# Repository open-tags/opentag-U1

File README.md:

# opentag U1

UWB distance and indoor positioning hardware for robots: KiCad design, Rust
firmware, host tools, enclosure CAD and bench test notes. Everything in this
repository is released under the [MIT License](LICENSE).

Product page and kits: <https://open-tags.com/products/u1/> ·
Documentation: <https://open-tags.com/docs/> ·
Measured performance: <https://open-tags.com/validation/>

## Contents

| Folder | What it holds |
| --- | --- |
| [`hardware/`](hardware/) | KiCad project for U1 PCB V2.2 (4 layers, STM32G474 + Qorvo DWM3000), schematic PDF, part list, and fabrication outputs (Gerbers + drill) |
| [`firmware/stm32g4/`](firmware/stm32g4/) | Embassy (Rust) firmware: two-way ranging, TDOA anchor/tag, USB serial, CAN FD, and board bring-up examples |
| [`firmware/twr_plot/`](firmware/twr_plot/) | Host-side plotting, localization, and calibration tools (Rust) |
| [`mechanical/`](mechanical/) | Enclosure STEP files (assembly, case, lid) and a printable case `.3mf`; also on [Onshape](https://cad.onshape.com/documents/432dec42a257744f3b8f22d9/w/829cba9d7a4b997211a6277e/e/23eb042ed87c06c15fa7c407) |
| [`testing/`](testing/) | Bench test notes for two-way ranging and TDOA |

The ROS 2 driver and the Python host scripts live with the website source at
[open-tags/open-tags.github.io](https://github.com/open-tags/open-tags.github.io)
(`ros2/` and `docs/scripts/`).

## Hardware

Open `hardware/opentag.kicad_pro` in KiCad 10. Footprints are embedded in the
board file. Three vendor 3D models are not redistributed here, so they appear
missing in the 3D viewer until you add them to `hardware/footprints/`:

- `1473790000--3DModel-STEP-764301.STEP`: Weidmüller 1473790000 terminal block (from Weidmüller)
- `3220-10-0300-00 3D.stp`: CNC Tech 3220-10-0300-00 SWD header (from CNC Tech)
- `v2 - dip_switch.step`: DIP switch body

`hardware/fabrication/` was generated from the board file with `kicad-cli`.

## Firmware

Requires Rust with the `thumbv7em-none-eabi` target and
[probe-rs](https://probe.rs) with an ST-Link or other SWD probe.

```sh
rustup target add thumbv7em-none-eabi
cd firmware/stm32g4
cargo run --release --bin twr_resp    # build, flash, and stream defmt logs
```

`tdoa_bench` needs `TDOA_ROLE=master` or `TDOA_ROLE=anchor` at build time.
Cargo fetches Embassy from GitHub at a pinned commit. See
[`firmware/README.md`](firmware/README.md) for the binaries, pinout, and
flashing, and [`firmware/RANGE_CAN.md`](firmware/RANGE_CAN.md) for the
range-over-CAN build.

## Third-party code

Several bring-up examples in `firmware/stm32g4/src/bin/` are adapted from the
[Embassy](https://github.com/embassy-rs/embassy) STM32G4 examples (MIT OR
Apache-2.0). Dependencies keep their own licenses; see each crate on crates.io.

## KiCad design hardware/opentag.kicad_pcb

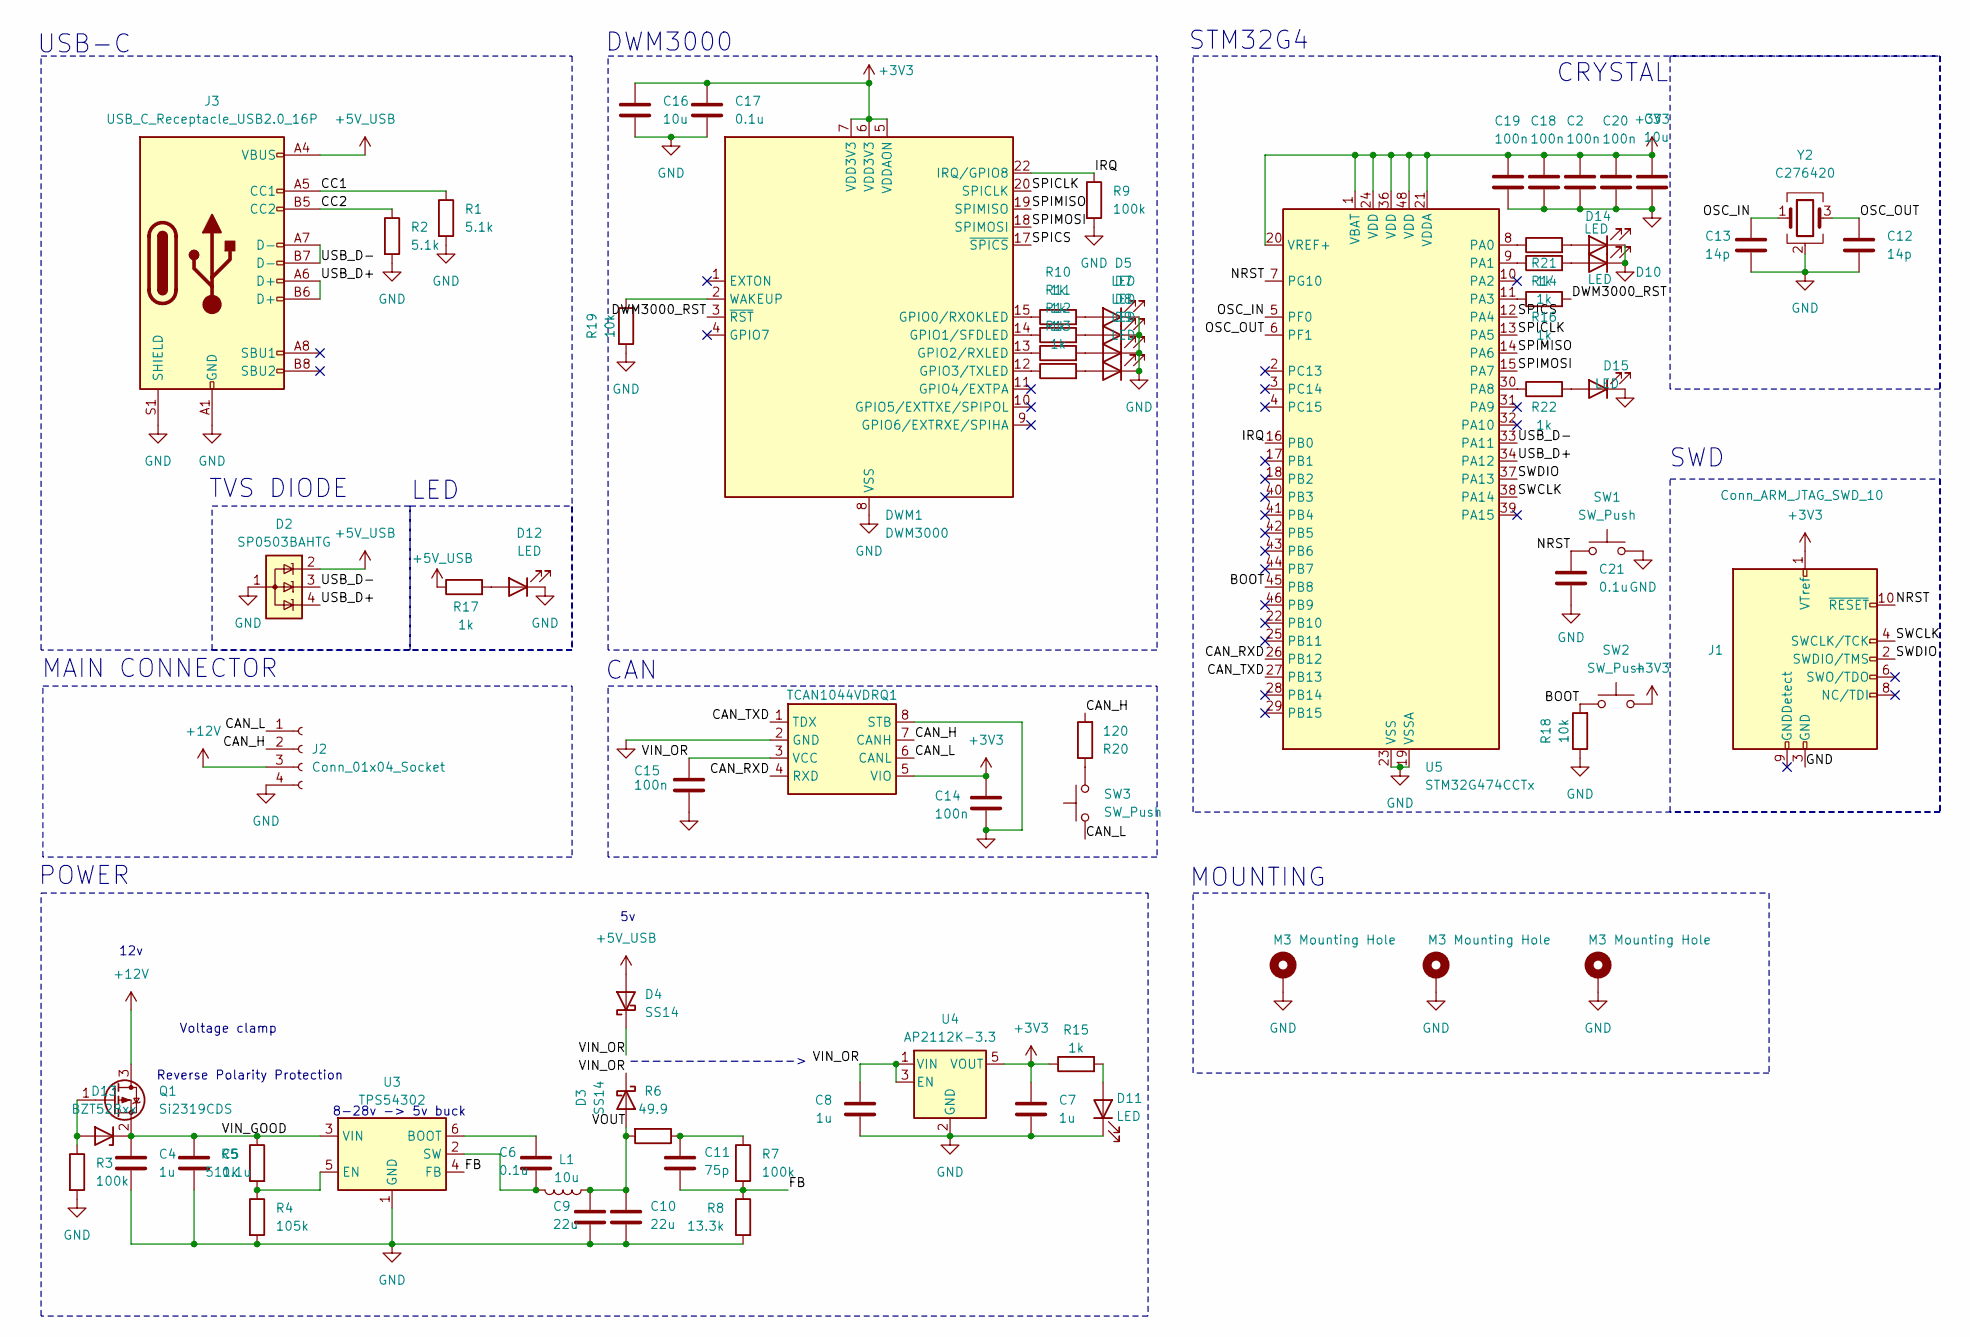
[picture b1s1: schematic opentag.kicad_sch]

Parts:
C2, C14, C15, C18, C19, C20: 100n; C_0402_1005Metric_Pad0.74x0.62mm_HandSolder; LCSC C307331
C3, C16: 10u; C_0402_1005Metric_Pad0.74x0.62mm_HandSolder; LCSC C315248
C4, C8: 1u; C_0402_1005Metric_Pad0.74x0.62mm_HandSolder; LCSC C1518208
C5, C6, C17, C21: 0.1u; C_0402_1005Metric_Pad0.74x0.62mm_HandSolder; LCSC C307331
C7: 1u; C_0402_1005Metric_Pad0.74x0.62mm_HandSolder; LCSC C29266
C9, C10: 22u; C_0402_1005Metric_Pad0.74x0.62mm_HandSolder; LCSC C105226
C11: 75p; C_0402_1005Metric_Pad0.74x0.62mm_HandSolder; LCSC C107010
C12, C13: 14p; C_0402_1005Metric_Pad0.74x0.62mm_HandSolder; LCSC C458857
D2: SP0503BAHTG; SOT-143; LCSC C3040626
D3, D4: SS14; D_SMA; LCSC C2480
D5, D7, D8, D9, D10, D11, D12, D14, D15: LED; LED_0402_1005Metric_Pad0.77x0.64mm_HandSolder; LCSC C130719
D13: BZT52Bxx; D_SOD-123F; LCSC C282531
DWM1: DWM3000; DWM1000; Mouser Part Number 772-DWM3000TR13; Digikey Part Number 2312-DWM3000TR13CT-ND
H1, H2, H3: M3 Mounting Hole; MountingHole_3.2mm_M3_Pad_Via
J1: Conn_ARM_JTAG_SWD_10; PinHeader_2x05_P1.27mm_Vertical_SMD; LCSC C42372555
J2: Conn_01x04_Socket; 4_WIRE_1473790000; Mouser Part Number 470-1473790000; Digikey Part Number 281-6806-1-ND
J3: USB_C_Receptacle_USB2.0_16P; USB_C_Receptacle_XKB_U262-16XN-4BVC11; LCSC C319148
L1: 10u; L_Sunlord_MWSA0503S; LCSC C408412
Q1: Si2319CDS; SOT-23; LCSC C5122036
R1, R2: 5.1k; R_0402_1005Metric_Pad0.72x0.64mm_HandSolder; LCSC C25905
R3, R7, R9: 100k; R_0402_1005Metric_Pad0.72x0.64mm_HandSolder; LCSC C25530
R4: 105k; R_0402_1005Metric_Pad0.72x0.64mm_HandSolder; LCSC C25742
R5: 511k; R_0402_1005Metric_Pad0.72x0.64mm_HandSolder; LCSC C64042
R6: 49.9; R_0402_1005Metric_Pad0.72x0.64mm_HandSolder; LCSC C325388
R8: 13.3k; R_0402_1005Metric_Pad0.72x0.64mm_HandSolder; LCSC C122547
R10, R11, R12, R13, R14, R15, R16, R17, R21, R22: 1k; R_0402_1005Metric_Pad0.72x0.64mm_HandSolder; LCSC C11702
R18, R19: 10k; R_0402_1005Metric_Pad0.72x0.64mm_HandSolder; LCSC C25744
R20: 120; R_0402_1005Metric_Pad0.72x0.64mm_HandSolder; LCSC C100218
SW1, SW2: SW_Push; SW_SPST_EVQP2_ShortPushTravel_H2.1mm; LCSC C79161
SW3: SW_Push; THS101J; LCSC C2758165
U1: TCAN1044VDRQ1; SOIC-8_3.9x4.9mm_P1.27mm; LCSC C1852061
U3: TPS54302; SOT-23-6; LCSC C311983
U4: AP2112K-3.3; SOT-23-5; LCSC C23380830
U5: STM32G474CCTx; LQFP-48_7x7mm_P0.5mm; LCSC C730124
Y2: C276420; Crystal_SMD_Abracon_ABM3B-4Pin_5.0x3.2mm; LCSC C276420

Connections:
+3V3: C2.1, C3.1, C7.1, C14.1, C16.1, C17.1, C18.1, C19.1, C20.1, DWM1.5 (VDDAON), DWM1.6 (VDD3V3), DWM1.7 (VDD3V3), J1.1 (VTref), R15.1, SW2.2, U1.5 (VIO), U4.5 (VOUT), U5.1 (VBAT), U5.20 (VREF+), U5.21 (VDDA), U5.24 (VDD), U5.36 (VDD), U5.48 (VDD)
+5V_USB: D2.2 (K), D4.2 (A), J3.A4 (VBUS), J3.A9 (VBUS), J3.B4 (VBUS), J3.B9 (VBUS), R17.1
+12V: J2.3, Q1.3 (D)
/BOOT: R18.2, SW2.1, U5.45 (PB8)
/CAN_H: J2.2, R20.2, U1.7 (CANH)
/CAN_L: J2.1, SW3.1, U1.6 (CANL)
/CAN_RXD: U1.4 (RXD), U5.26 (PB12)
/CAN_TXD: U1.1 (TDX), U5.27 (PB13)
/CC1: J3.A5 (CC1), R1.1
/CC2: J3.B5 (CC2), R2.1
/DWM3000_RST: DWM1.3 (~RST), R16.2
/FB: C11.2, R7.2, R8.1, U3.4 (FB)
/IRQ: DWM1.22 (IRQ/GPIO8), R9.1, U5.16 (PB0)
/NRST: C21.1, J1.10 (~RESET), SW1.1, U5.7 (PG10)
/OSC_IN: C13.1, U5.5 (PF0), Y2.1
/OSC_OUT: C12.1, U5.6 (PF1), Y2.3
/SPICLK: DWM1.20 (SPICLK), U5.13 (PA5)
/SPICS: DWM1.17 (~SPICS), U5.12 (PA4)
/SPIMISO: DWM1.19 (SPIMISO), U5.14 (PA6)
/SPIMOSI: DWM1.18 (SPIMOSI), U5.15 (PA7)
/SWCLK: J1.4 (SWCLK/TCK), U5.38 (PA14)
/SWDIO: J1.2 (SWDIO/TMS), U5.37 (PA13)
/USB_D+: D2.4 (K), J3.A6 (D+), J3.B6 (D+), U5.34 (PA12)
/USB_D-: D2.3 (K), J3.A7 (D-), J3.B7 (D-), U5.33 (PA11)
/VIN_GOOD: C4.1, C5.1, D13.1 (K), Q1.2 (S), R5.1, U3.3 (VIN)
/VIN_OR: C8.1, C15.1, D3.1 (K), D4.1 (K), U1.3 (VCC), U4.1 (VIN), U4.3 (EN)
/VOUT: C9.1, C10.1, D3.2 (A), L1.1, R6.2
GND: C2.2, C3.2, C4.2, C5.2, C7.2, C8.2, C9.2, C10.2, C12.2, C13.2, C14.2, C15.2, C16.2, C17.2, C18.2, C19.2, C20.2, C21.2, D2.1 (A), D5.1 (K), D7.1 (K), D8.1 (K), D9.1 (K), D10.1 (K), D11.1 (K), D12.1 (K), D14.1 (K), D15.1 (K), DWM1.8 (VSS), DWM1.16 (VSS), DWM1.21 (VSS), DWM1.23 (VSS), DWM1.24 (VSS), H1.1 (1_1), H2.1 (1_1), H3.1 (1_1), J1.3 (GND), J1.5 (GND), J2.4, J3.A1 (GND), J3.A12 (GND), J3.B1 (GND), J3.B12 (GND), J3.S1 (SHIELD), R1.2, R2.2, R3.2, R4.2, R8.2, R9.2, R18.1, R19.1, SW1.2, U1.2 (GND), U1.8 (STB), U3.1 (GND), U4.2 (GND), U5.19 (VSSA), U5.23 (VSS), U5.35 (VSS), U5.47 (VSS), Y2.2 (G), Y2.4 (G)
unnamed: C11.1, R6.1, R7.1
unnamed: D5.2 (A), R10.2
unnamed: D7.2 (A), R11.2
unnamed: D8.2 (A), R12.2
unnamed: D9.2 (A), R13.2
unnamed: D10.2 (A), R14.2
unnamed: D11.2 (A), R15.2
unnamed: D12.2 (A), R17.2
unnamed: D13.2 (A), Q1.1 (G), R3.1
unnamed: D14.2 (A), R21.2
unnamed: D15.2 (A), R22.2
unnamed: DWM1.15 (GPIO0/RXOKLED), R10.1
unnamed: DWM1.14 (GPIO1/SFDLED), R11.1
unnamed: DWM1.13 (GPIO2/RXLED), R12.1
unnamed: DWM1.12 (GPIO3/TXLED), R13.1
unnamed: DWM1.2 (WAKEUP), R19.2
unnamed: R20.1, SW3.2
unnamed: C6.1, U3.6 (BOOT)
unnamed: R4.1, R5.2, U3.5 (EN)
unnamed: C6.2, L1.2, U3.2 (SW)
unnamed: R21.1, U5.8 (PA0)
unnamed: R14.1, U5.9 (PA1)
unnamed: R16.1, U5.11 (PA3)
unnamed: R22.1, U5.30 (PA8)

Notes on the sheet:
MOUNTING
SWD
LED
DWM3000
TVS DIODE
--------------->
Reverse Polarity Protection
8-28v -> 5v buck
Voltage clamp
CAN
POWER
USB-C
12v
STM32G4
CRYSTAL
MAIN CONNECTOR

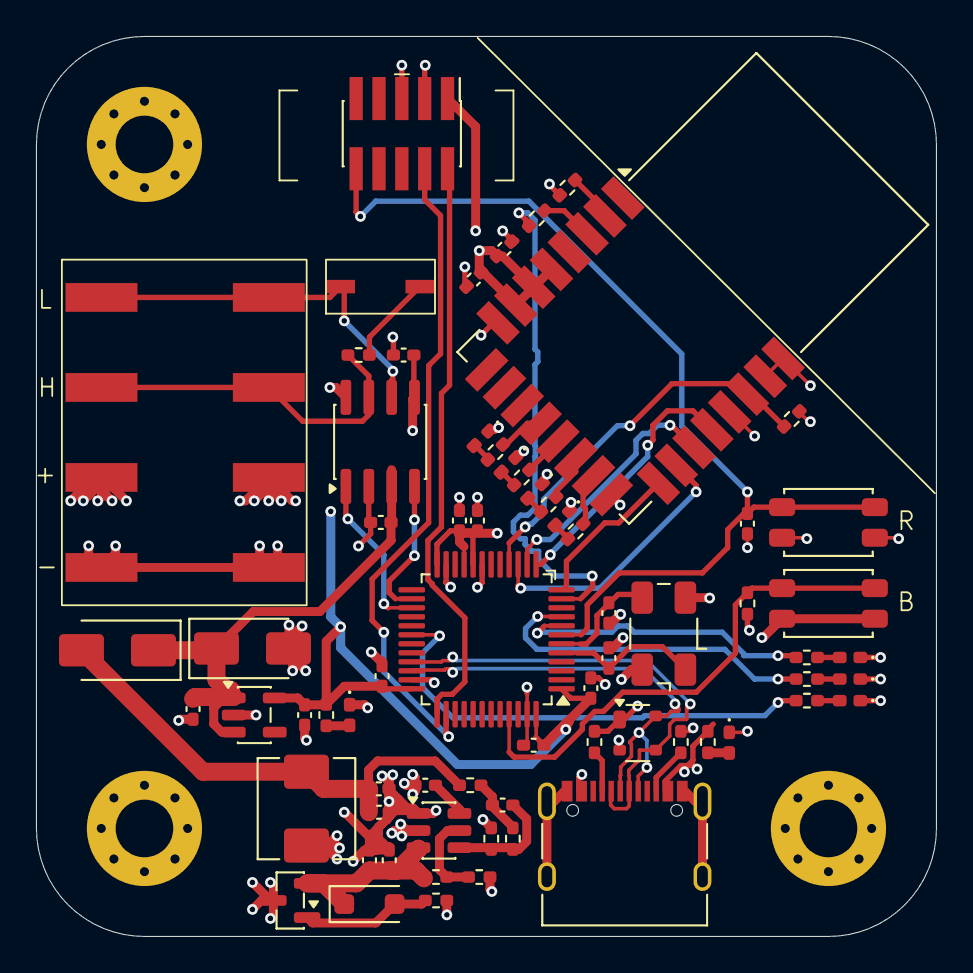
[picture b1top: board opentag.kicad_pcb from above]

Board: 4 copper layers, 50.0 x 50.0 mm, 72 parts (0 on the bottom side), 52 nets.

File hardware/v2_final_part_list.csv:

Comment,Designator,Footprint,JLCPCB Part #,Qty,Ext.Price($)
LED,"D14,D5,D7,D8,D9",0402,C965793,62,0.49
AP2112K-3.3,U4,SOT-23-5,C23380830,12,1.29
Si2319CDS,Q1,SOT-23,C5122036,12,1.11
511k,R5,0402,C64042,20,0.02
SW_Push,"SW1,SW2",SW_SPST_EVQP2_ShortPushTravel_H2.1mm,C79161,20,7.51
BZT52Bxx,D13,D_SOD-123F,C282531,14,0.63
105k,R4,0402,C25742,20,0.01
LED,D15,0402,C25503345,22,0.18
LED,D10,0402,C25503856,20,0.26
Conn_ARM_JTAG_SWD_10,J1,PinHeader_2x05_P1.27mm_Vertical_SMD,C42372555,10,1.91
22u,"C10,C9",0402,C3845593,21,2.95
LED,"D11,D12",0402,C20613596,32,0.36
SP0503BAHTG,D2,SOT-143,C3040626,12,1.13
10u,"C16,C3",0402,C315248,32,0.29
120,R20,0402,C25079,20,0.02
10u,L1,L_Sunlord_MWSA0503S,C408412,12,2.03
75p,C11,0402,C107010,20,0.02
TPS54302,U3,SOT-23-6,C311983,10,2.44
USB_C_Receptacle_USB2.0_16P,J3,USB_C_Receptacle_XKB_U262-16XN-4BVC11,C319148,10,3.70
SS14,"D3,D4",D_SMA,C2480,30,0.50
100k,"R3,R7,R9",0402,C25530,40,0.03
1k,"R10,R11,R12,R13,R14,R15,R16,R17,R21,R22",0402,C11702,110,0.11
1u,"C4,C7,C8",0402,C1518208,34,1.03
49.9,R6,0402,C325388,20,0.05
13.3k,R8,0402,C122547,20,0.02
5.1k,"R1,R2",0402,C25905,30,0.03
SW_Push,SW3,THS101J,C2758165,10,5.99
Crystal_GND24,Y2,Crystal_SMD_Abracon_ABM3B-4Pin_5.0x3.2mm,C276420,10,6.18
14p,"C12,C13",0402,C458857,30,0.06
TCAN1044VDRQ1,U1,SOIC-8_3.9x4.9mm_P1.27mm,C1852061,10,3.39
100n,"C17,C21,C5,C6,C14,C15,C18,C19,C2,C20",0402,C307331,110,0.46
10k,"R18,R19",0402,C25744,30,0.04
STM32G474CCTx,U5,LQFP-48_7x7mm_P0.5mm,C730124,10,29.39

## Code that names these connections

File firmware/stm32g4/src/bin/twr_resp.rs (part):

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    }
    let p = embassy_stm32::init(config);
    #[cfg(feature = "range-can")]
    let can = range_can::configure(p.FDCAN2, p.PB12, p.PB13);

    // Pull the patched calibration default out of flash. read_volatile
    // prevents the optimizer from constant-folding it (which would
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
    info!("twr_resp starting (calib={})", initial_calib);

    let mut rst = Output::new(p.PA3, Level::Low, Speed::Low);
    Timer::after_millis(10).await;
    rst.set_high();
    Timer::after_millis(5).await;
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    let mut spi_config = spi::Config::default();
    spi_config.frequency = Hertz(4_000_000);
    let spi = Spi::new(
        p.SPI1, p.PA5, p.PA7, p.PA6, p.DMA1_CH3, p.DMA1_CH2, Irqs, spi_config,
    );
    let cs = Output::new(p.PA4, Level::High, Speed::High);
    let spi_dev = ExclusiveDevice::new(spi, cs, Delay).unwrap();

    let dw3000 = DW3000::new(spi_dev);
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    }
    dw3000.gpio_config_clocks().await.expect("gpio clocks");

    let driver = Driver::new(p.USB, Irqs, p.PA12, p.PA11);
    let mut usb_config = embassy_usb::Config::new(0xc0de, 0xcafe);
    usb_config.manufacturer = Some("opentags");
    usb_config.product = Some("opentags TWR Responder");
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
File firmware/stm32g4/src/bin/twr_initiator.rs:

#![no_std]
#![no_main]

// TWR Initiator — Qorvo APS013 Double-Sided Two-Way Ranging (DS-TWR)
//
// 3-message exchange:
//   Msg 1  Poll     Initiator → Responder    seq                     (4 B)
//   Msg 2  Response Responder → Initiator    seq + T2(5B) + T3(5B)   (14 B)
//   Msg 3  Final    Initiator → Responder    seq + T1(5B) + T4(5B) + T5(5B) (19 B)
//
// Timestamps (all 40-bit DW3000 DTU, little-endian 5 bytes):
//   T1 = initiator TX Poll
//   T2 = responder RX Poll      (embedded in Response)
//   T3 = responder TX Response  (embedded in Response, via delayed TX)
//   T4 = initiator RX Response
//   T5 = initiator TX Final     (pre-calculated, embedded in Final, via delayed TX)
//   T6 = responder RX Final     (used at responder to compute distance)
//
// Distance is computed and logged by the responder (it holds all 6 timestamps).
// Formula (APS013):
//   tof = (Tround1 × Tround2 - Treply1 × Treply2) / (Tround1 + Tround2 + Treply1 + Treply2)
//   where  Tround1 = T4-T1,  Tround2 = T6-T3,  Treply1 = T3-T2,  Treply2 = T5-T4
//
// Pinout:
//   PA3=RST  PA4=CS  PA5=SCK  PA6=MISO  PA7=MOSI
//   PA0=Poll TX LED  PA1=exchange OK LED  PA8=miss/error LED

use defmt::*;
use embassy_executor::Spawner;
use embassy_stm32::gpio::{Level, Output, Speed};
use embassy_stm32::rcc::{Hse, HseMode, Pll, PllMul, PllPreDiv, PllRDiv, PllSource, Sysclk};
use embassy_stm32::spi::{self, Spi};
use embassy_stm32::time::Hertz;
use embassy_stm32::{bind_interrupts, dma, peripherals};
use embassy_time::{Delay, Timer};
use embedded_hal_bus::spi::ExclusiveDevice;
use dw3000_ng::{Config, DW3000, configs::UwbChannel, hl::SendTime};
use dw3000_ng::time::{Instant as DwInstant, Duration as DwDuration};
use nb;
use {defmt_rtt as _, panic_probe as _};

bind_interrupts!(struct Irqs {
    DMA1_CHANNEL2 => dma::InterruptHandler<peripherals::DMA1_CH2>;
    DMA1_CHANNEL3 => dma::InterruptHandler<peripherals::DMA1_CH3>;
});

const POLL_ID:   &[u8] = &[0xDE, 0xCA, 0x01];
const RESP_ID:   &[u8] = &[0xDE, 0xCA, 0x02];
const FINAL_ID:  &[u8] = &[0xDE, 0xCA, 0x03];

// Delay from Response RX (T4) to Final TX (T5).
// The old 10 ms value worked but was marginal on v2: occasional missed Finals
// showed up at the responder. Keep this comfortably above RX teardown + SPI
// setup + delayed-TX programming time.
const TREPLY2_NS: u32 = 25_000_000; // 25 ms

fn pack_ts(ts: u64, buf: &mut [u8]) {
    let b = ts.to_le_bytes();
    buf[..5].copy_from_slice(&b[..5]);
}

fn unpack_ts(buf: &[u8]) -> u64 {
    u64::from_le_bytes([buf[0], buf[1], buf[2], buf[3], buf[4], 0, 0, 0])
}

fn align512(raw: u64) -> DwInstant {
    DwInstant::new((raw + 511) & !511u64).unwrap()
}

#[embassy_executor::main]
async fn main(_spawner: Spawner) {
    let mut config = embassy_stm32::Config::default();
    {
        config.rcc.hse = Some(Hse { freq: Hertz(8_000_000), mode: HseMode::Oscillator });
        config.rcc.pll = Some(Pll {
            source: PllSource::HSE,
            prediv: PllPreDiv::DIV2,
            mul: PllMul::MUL85,
            divp: None, divq: None,
            divr: Some(PllRDiv::DIV2),
        });
        config.rcc.sys = Sysclk::PLL1_R;
    }
    let p = embassy_stm32::init(config);

    info!("TWR Initiator (DS-TWR) starting");

    let mut poll_led = Output::new(p.PA0, Level::Low, Speed::Low);
    let mut ok_led = Output::new(p.PA1, Level::Low, Speed::Low);
    let mut err_led = Output::new(p.PA8, Level::Low, Speed::Low);

    let mut rst = Output::new(p.PA3, Level::Low, Speed::Low);
    Timer::after_millis(10).await;
    rst.set_high();
    Timer::after_millis(5).await;

    let mut spi_config = spi::Config::default();
    spi_config.frequency = Hertz(4_000_000);
    let spi = Spi::new(p.SPI1, p.PA5, p.PA7, p.PA6, p.DMA1_CH3, p.DMA1_CH2, Irqs, spi_config);
    let cs = Output::new(p.PA4, Level::High, Speed::High);
    let spi_dev = ExclusiveDevice::new(spi, cs, Delay).unwrap();

    let dw3000 = DW3000::new(spi_dev);
    let dw3000 = dw3000.init().await.expect("DW3000 init failed");
    let dw_config = Config { channel: UwbChannel::Channel9, ..Config::default() };
    let mut dw3000 = dw3000.config(dw_config, Delay).await.expect("DW3000 config failed");

    for pin in 0..4u8 {
        dw3000.gpio_config_mode(pin, 1).await.expect("gpio mode failed");
    }
    dw3000.gpio_config_clocks().await.expect("gpio clocks failed");

    info!("DW3000 ready — starting DS-TWR exchange loop");

    let mut seq: u8 = 0;
    loop {
        // ── MSG 1: Poll ──────────────────────────────────────────────────────
        let poll = [POLL_ID[0], POLL_ID[1], POLL_ID[2], seq];
        poll_led.set_high();
        let mut sending = dw3000.send(&poll, SendTime::Now, dw_config).await.expect("poll send failed");

        let t1: DwInstant = loop {
            match sending.s_wait().await {
                Ok(ts) => break ts,
                Err(nb::Error::WouldBlock) => Timer::after_micros(100).await,
                Err(nb::Error::Other(_)) => core::panic!("poll s_wait failed"),
            }
        };
        dw3000 = sending.finish_sending().await.unwrap_or_else(|(_, _)| core::panic!("finish_sending"));

        // ── MSG 2: Receive Response ──────────────────────────────────────────
        let mut receiving = dw3000.receive(dw_config).await.expect("receive failed");
        let mut rx_buf = [0u8; 128];

        let deadline = embassy_time::Instant::now() + embassy_time::Duration::from_millis(500);
        let rx_data = loop {
            if embassy_time::Instant::now() > deadline { break None; }
            match receiving.r_wait_buf(&mut rx_buf).await {
                Ok((len, ts, _)) => break Some((len, ts)),
                Err(nb::Error::WouldBlock) => Timer::after_micros(100).await,
                Err(nb::Error::Other(_)) => { error!("RX error on response"); break None; }
            }
        };
        dw3000 = receiving.finish_receiving().await.unwrap_or_else(|(_, _)| core::panic!("finish_receiving"));

        let Some((len, t4)) = rx_data else {
            info!("seq={} no response (timeout)", seq);
            poll_led.set_low();
            err_led.set_high();
            Timer::after_millis(200).await;
            err_led.set_low();
            seq = seq.wrapping_add(1);
            Timer::after_millis(500).await;
            continue;
        };

        // Find Response payload and extract T2, T3
        let frame = &rx_buf[..len];
        let Some(pos) = frame.windows(3).position(|w| w == RESP_ID) else {
            info!("seq={} unexpected frame (len={})", seq, len);
            poll_led.set_low();
            err_led.set_high();
            Timer::after_millis(200).await;
            err_led.set_low();
            seq = seq.wrapping_add(1);
            Timer::after_millis(200).await;
            continue;
        };
        let data = &frame[pos..];
        if data.len() < 14 {
            warn!("seq={} response too short", seq);
            poll_led.set_low();
            err_led.set_high();
            Timer::after_millis(200).await;
            err_led.set_low();
            seq = seq.wrapping_add(1);
            Timer::after_millis(200).await;
            continue;
        }
        let _t2 = unpack_ts(&data[4..]);
        let _t3 = unpack_ts(&data[9..]);

        // ── MSG 3: Final ─────────────────────────────────────────────────────
        // T5 = T4 + TREPLY2, aligned to 512-tick boundary (required by DX_TIME)
        let t5 = align512((t4 + DwDuration::from_nanos(TREPLY2_NS)).value());

        let mut final_msg = [0u8; 19];
        final_msg[0] = FINAL_ID[0];
        final_msg[1] = FINAL_ID[1];
        final_msg[2] = FINAL_ID[2];
        final_msg[3] = seq;
        pack_ts(t1.value(), &mut final_msg[4..]);
        pack_ts(t4.value(), &mut final_msg[9..]);
        pack_ts(t5.value(), &mut final_msg[14..]);

        let mut sending = dw3000.send(&final_msg, SendTime::Delayed(t5), dw_config).await.expect("final send failed");

        let tx_ok = loop {
            match sending.s_wait().await {
                Ok(_) => break true,
                Err(nb::Error::WouldBlock) => Timer::after_micros(100).await,
                Err(nb::Error::Other(_)) => {
                    warn!("seq={} Final TX too late — increase TREPLY2_NS", seq);
                    break false;
                }
            }
        };
        dw3000 = sending.finish_sending().await.unwrap_or_else(|(_, _)| core::panic!("finish_sending"));

        if tx_ok {
            info!("seq={} exchange done — see responder for distance", seq);
            poll_led.set_low();
            ok_led.set_high();
            Timer::after_millis(200).await;
            ok_led.set_low();
        } else {
            poll_led.set_low();
            err_led.set_high();
            Timer::after_millis(200).await;
            err_led.set_low();
        }

        seq = seq.wrapping_add(1);
        Timer::after_millis(500).await;
    }
}
